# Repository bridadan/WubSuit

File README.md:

WubSuit
=======

EECS 373 final project

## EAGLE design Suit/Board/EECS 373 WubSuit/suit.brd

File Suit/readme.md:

This is where the suit code/files live...

Protocol
========
TX: | 0x00 | 0x(xdata) | 0x(ydata) | 0x(zdata) | 0x(flex) | 0x(height) | 

RX: every byte sent to LED controller 

DIO0: Note capture button 

DIO1: Left foot piezo trigger 

DIO2: Right foot piezo trigger 

DIO3: BTN 1 

DIO4: BTN 2 

DIO5: BTN 3

DIO6: BTN 4 

Arduino
=======
Contains the arduino code / files for programming on the ATMEGA328

Board
=======
Eagle files for the custom circuitboard

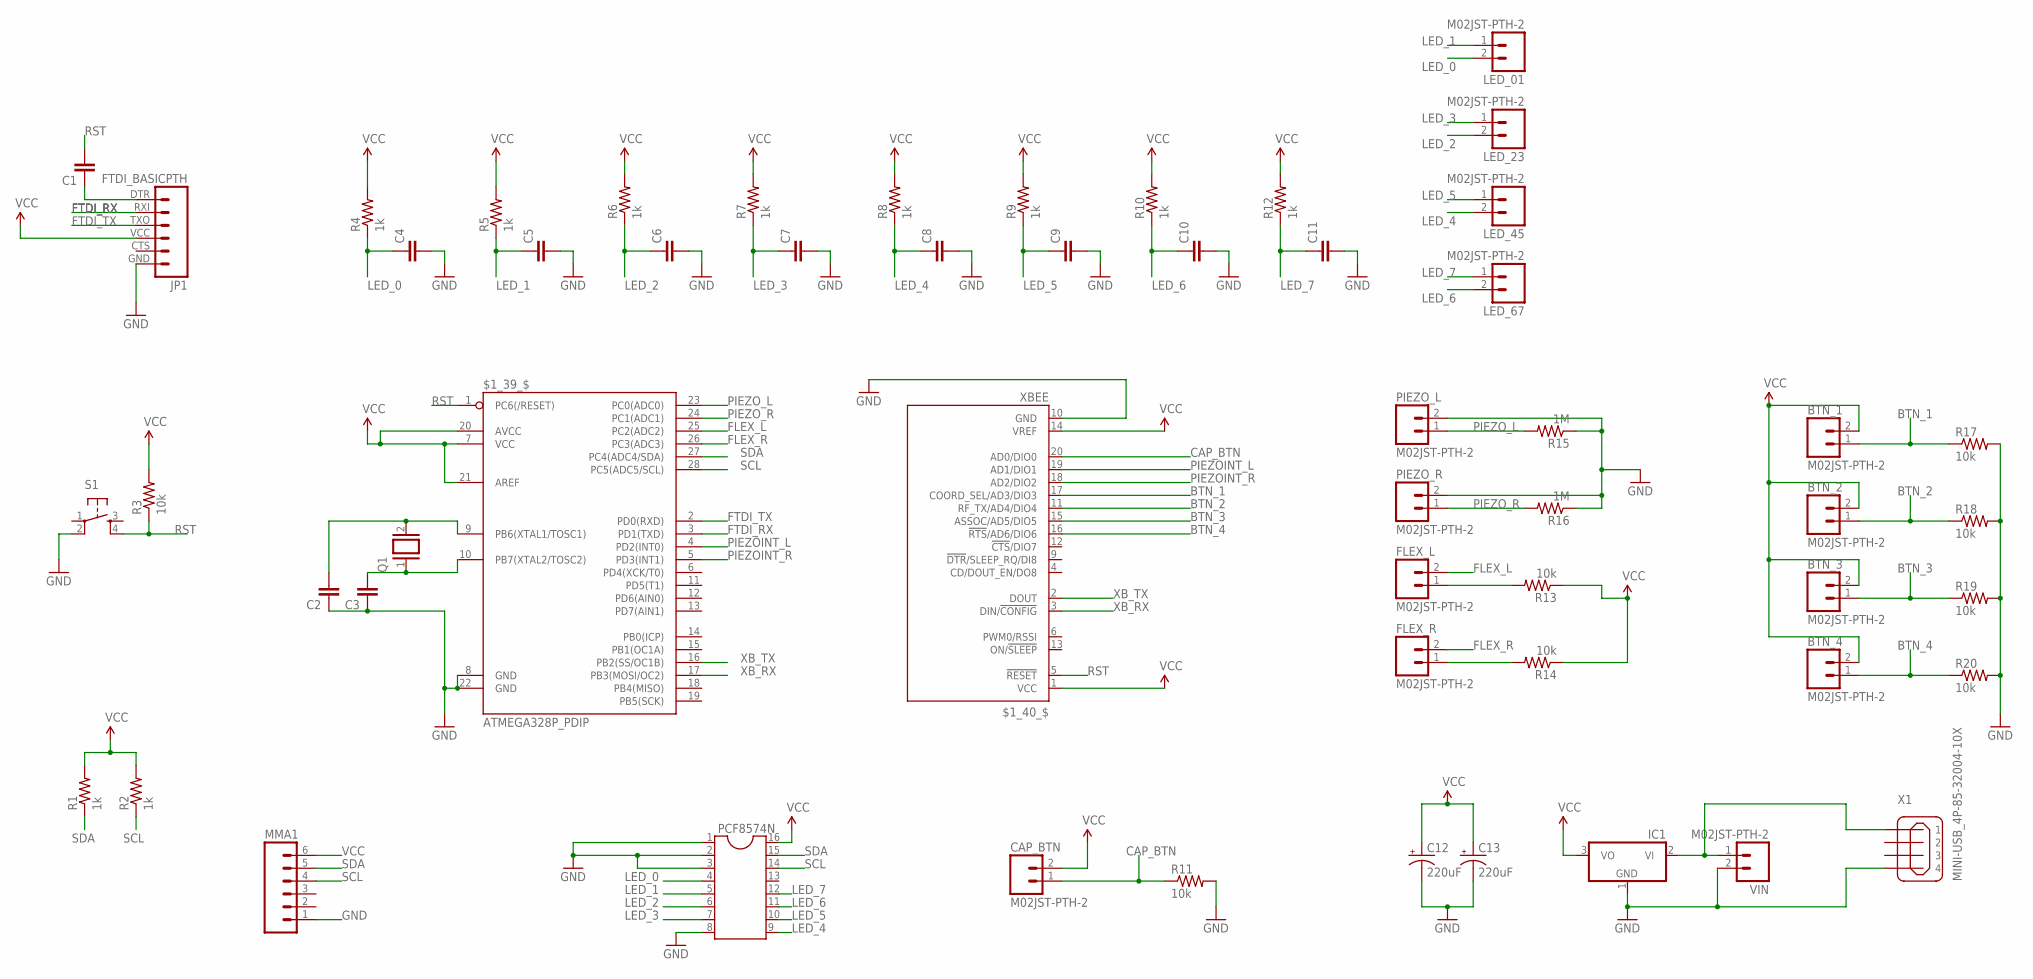
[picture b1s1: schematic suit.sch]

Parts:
$1_39_$: ATMEGA328P_PDIP; DIL28-3
$1_40_$: XBEE
BTN_1, BTN_2, BTN_3, BTN_4: M02JST-PTH-2; JST-2-PTH
C1, C2, C3, C4, C5, C6, C7, C8, C9, C10, C11: CAPEZ; CAP-PTH-SMALLEZ
C12, C13: 220uF; B45181A
CAP_BTN: M02JST-PTH-2; JST-2-PTH
FLEX_L: M02JST-PTH-2; JST-2-PTH
FLEX_R: M02JST-PTH-2; JST-2-PTH
IC1: 79L05Z; TO92
JP1: FTDI_BASICPTH; FTDI_BASIC
LED_01, LED_23, LED_45, LED_67: M02JST-PTH-2; JST-2-PTH
MMA1: M06FEMALE_LOCK; 1X06_FEMALE_LOCK.010
PCF8574N: DIL16S; SOCKET-16
PIEZO_L: M02JST-PTH-2; JST-2-PTH
PIEZO_R: M02JST-PTH-2; JST-2-PTH
Q1: XTAL/S; QS
R1, R2, R4, R5, R6, R7, R8, R9, R10, R12: 1k; 0207/10
R3, R11, R13, R14, R17, R18, R19, R20: 10k; 0207/10
R15, R16: 1M; 0207/10
S1: TAC_SWITCHPTH; TACTILE-PTH
VIN: M02JST-PTH-2; JST-2-PTH
X1: MINI-USB_4P-85-32004-10X; 85-32004-10X

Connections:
BTN_1: $1_40_$.17 (COORD_SEL/AD3/DIO3), BTN_1.1, R17.1
BTN_2: $1_40_$.11 (RF_TX/AD4/DIO4), BTN_2.1, R18.1
BTN_3: $1_40_$.15 (ASSOC/AD5/DIO5), BTN_3.1, R19.1
BTN_4: $1_40_$.16 (!RTS!/AD6/DIO6), BTN_4.1, R20.1
CAP_BTN: $1_40_$.20 (AD0/DIO0), CAP_BTN.1, R11.1
FLEX_L: $1_39_$.25 (PC2(ADC2)), FLEX_L.2
FLEX_R: $1_39_$.26 (PC3(ADC3)), FLEX_R.2
FTDI_RX: $1_39_$.3 (PD1(TXD)), JP1.RXI (2)
FTDI_TX: $1_39_$.2 (PD0(RXD)), JP1.TXO (3)
GND: $1_39_$.8 (GND), $1_39_$.22 (GND), $1_40_$.10 (GND), C2.1, C3.1, C4.2, C5.2, C6.2, C7.2, C8.2, C9.2, C10.2, C11.2, C12.-, C13.-, IC1.1 (GND), JP1.GND (6), MMA1.1, PCF8574N.1, PCF8574N.2, PCF8574N.3, PCF8574N.8, PIEZO_L.2, PIEZO_R.2, R11.2, R15.1, R16.1, R17.2, R18.2, R19.2, R20.2, S1.2, VIN.2, X1.4
LED_0: C4.1, LED_01.2, PCF8574N.4, R4.1
LED_1: C5.1, LED_01.1, PCF8574N.5, R5.1
LED_2: C6.1, LED_23.2, PCF8574N.6, R6.1
LED_3: C7.1, LED_23.1, PCF8574N.7, R7.1
LED_4: C8.1, LED_45.2, PCF8574N.9, R8.1
LED_5: C9.1, LED_45.1, PCF8574N.10, R9.1
LED_6: C10.1, LED_67.2, PCF8574N.11, R10.1
LED_7: C11.1, LED_67.1, PCF8574N.12, R12.1
unnamed: FLEX_L.1, R13.2
unnamed: FLEX_R.1, R14.2
unnamed: C1.1, JP1.DTR (1)
unnamed: $1_39_$.10 (PB7(XTAL2/TOSC2)), C3.2, Q1.1
unnamed: $1_39_$.9 (PB6(XTAL1/TOSC1)), C2.2, Q1.2
unnamed: IC1.2 (VI), VIN.1, X1.1
PIEZOINT_L: $1_39_$.4 (PD2(INT0)), $1_40_$.19 (AD1/DIO1)
PIEZOINT_R: $1_39_$.5 (PD3(INT1)), $1_40_$.18 (AD2/DIO2)
PIEZO_L: $1_39_$.23 (PC0(ADC0)), PIEZO_L.1, R15.2
PIEZO_R: $1_39_$.24 (PC1(ADC1)), PIEZO_R.1, R16.2
RST: $1_39_$.1 (PC6(/RESET)), $1_40_$.5 (!RESET), C1.2, R3.1, S1.4
SCL: $1_39_$.28 (PC5(ADC5/SCL)), MMA1.4, PCF8574N.14, R2.1
SDA: $1_39_$.27 (PC4(ADC4/SDA)), MMA1.5, PCF8574N.15, R1.1
VCC: $1_39_$.7 (VCC), $1_39_$.20 (AVCC), $1_39_$.21 (AREF), $1_40_$.1 (VCC), $1_40_$.14 (VREF), BTN_1.2, BTN_2.2, BTN_3.2, BTN_4.2, C12.+, C13.+, CAP_BTN.2, IC1.3 (VO), JP1.VCC (4), MMA1.6, PCF8574N.16, R1.2, R2.2, R3.2, R4.2, R5.2, R6.2, R7.2, R8.2, R9.2, R10.2, R12.2, R13.1, R14.1
XB_RX: $1_39_$.17 (PB3(MOSI/OC2)), $1_40_$.3 (DIN/!CONFIG)
XB_TX: $1_39_$.16 (PB2(SS/OC1B)), $1_40_$.2 (DOUT)

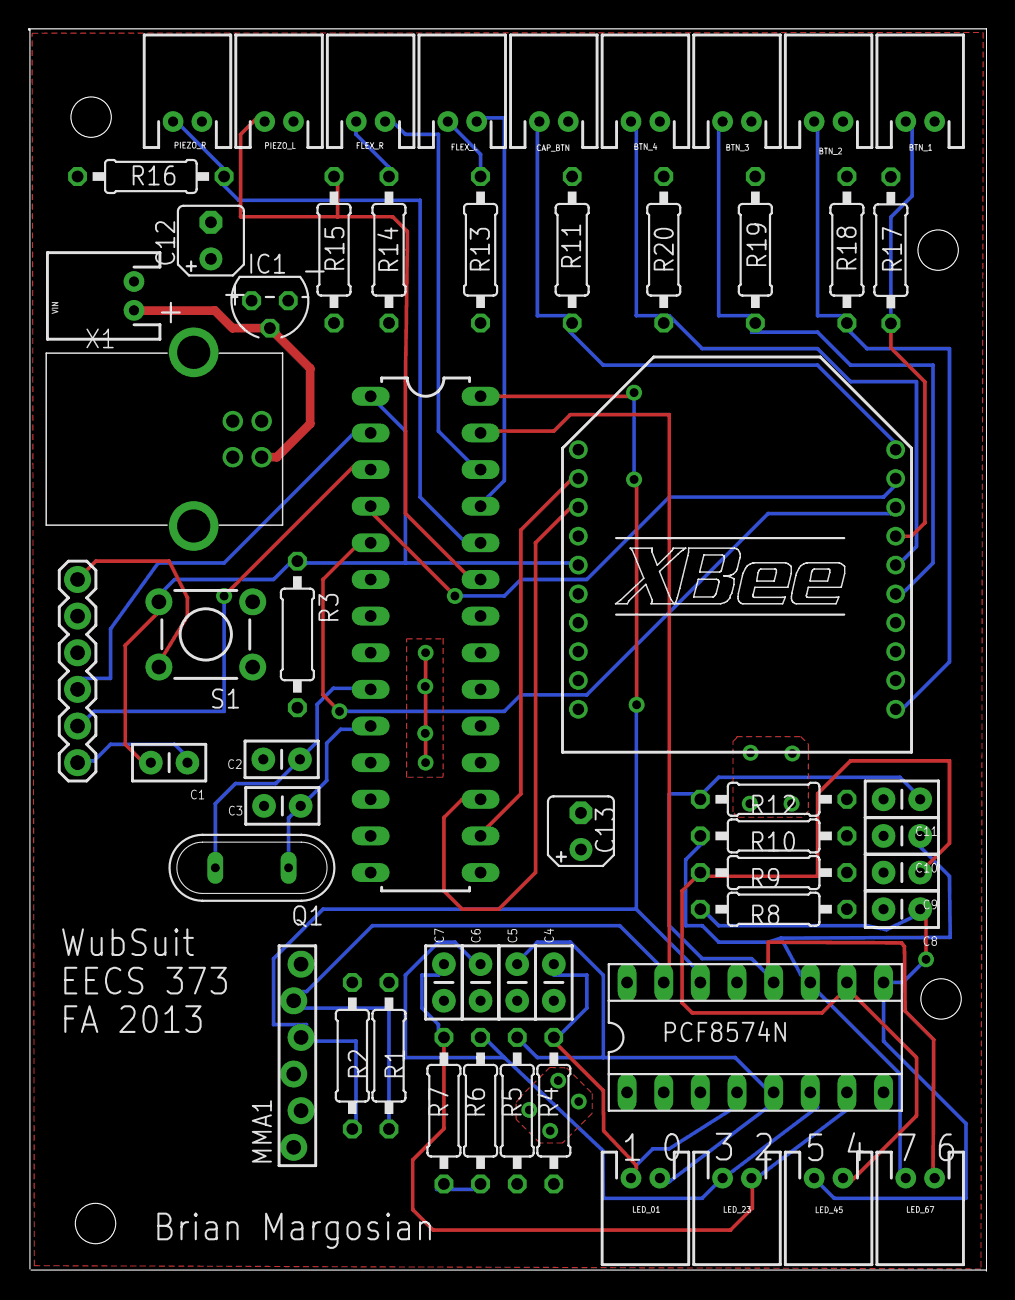
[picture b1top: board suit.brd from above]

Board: 2 copper layers, 66.4 x 86.1 mm, 56 parts (0 on the bottom side), 34 nets.

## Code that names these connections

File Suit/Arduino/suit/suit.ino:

#include <SimpleTimer.h>

#include <SoftwareSerial.h>
#include <Wire.h> //I2C

SoftwareSerial Xbee(10, 11); // RX, TX
SimpleTimer timer;
SimpleTimer resetTime;

#define DEBUG //unset if not debugging

#define PRECISION 0x02 //0x00 = 2G, 0x01 = 4G, 0x02 = 8G

#define LEDOUT_ADDR 0x20
#define ACCEL_ADDR 0x1D
#define ACCEL_X_MSB 0x01
#define ACCEL_CTRL 0x2A
#define ACCEL_XYZCFG 0x0E

#define PIEZO_L A0
#define PIEZO_R A1
#define FLEX_L A2
#define FLEX_R A3

#define SONAR 7
#define LEDPIN 13
#define TAP_L 2
#define TAP_R 3

#define FLEX_LOW 200
#define FLEX_HIGH 500
#define SONAR_LOW 0
#define SONAR_HIGH 72
#define THRESHOLD 50

byte Ax = 0x00;
byte Ay = 0x00;
byte Az = 0x00;
byte flex = 0x00;
byte height = 0x00;

boolean accel = true;

void setup()  
{
  Wire.begin(); //i2c master A5:SCL A4:SDA
  timer.setInterval(50,sendPacket);
  resetTime.setInterval(5000,softReset);
  
  // Open local serial port for debugging:
  Serial.begin(115200);

  // Open XBee serial for mass data communication
  Xbee.begin(115200);
  
  //Configure pins
  pinMode(LEDPIN,OUTPUT);
  pinMode(SONAR,INPUT);
  pinMode(TAP_L,OUTPUT);
  pinMode(TAP_R,OUTPUT);
  
  //turn the default 0xFF LEDs to all off
  setLEDs(0x00);
  
  //enable the arduino watchdog for 5 seconds.
  //wdt_enable (WDTO_4S);
  
  //init accel
  initAccel();
}

void loop()
{
  timer.run();
  resetTime.run();
  printDebug();
  updateAccel(Ax,Ay,Az);
  
  //write every recieved xbee byte to the leds
  while(Xbee.available()){
    setLEDs(Xbee.read());
  }
  int tap = 0;
  if((tap=analogRead(PIEZO_L)) > THRESHOLD){
    Serial.print("Left tap: ");
    Serial.println(tap);
    pulse(TAP_L);
    pulse(LEDPIN);
  }
  
  if((tap=analogRead(PIEZO_R)) > THRESHOLD){
    Serial.print("Right tap: ");
    Serial.println(tap);
    pulse(TAP_R);
    pulse(LEDPIN);
  }
  byte lastheight = height;
  height = map(pulseIn(SONAR,HIGH,10000)/147,SONAR_LOW,SONAR_HIGH,0,254);
  if(height == 0)
    height = lastheight; //pulseIn broke, so keep valid data.
  flex = map(analogRead(FLEX_L),FLEX_LOW,FLEX_HIGH,0,254);
}

void setLEDs(byte data){
  //Writes a byte to the LED strip via i2c
    Wire.beginTransmission(LEDOUT_ADDR);
    Wire.write(data); //active high
    Wire.endTransmission();
    
    #ifdef DEBUG
      Serial.print("Wrote LEDs to: ");
      Serial.println((byte)(data),BIN);
    #endif
}

void sendPacket(){
  //send a packet of data to UART 
  if(Xbee.overflow()){
   Serial.println("Xbee overflow");
   return; 
  }
  noInterrupts();
  Xbee.write((byte)0xFF);
  Xbee.write((byte)0xA0);
  Xbee.write((byte)0xB7);
  Xbee.write(Ax);
  Xbee.write(Ay);
  Xbee.write(Az);
  Xbee.write(flex);
  Xbee.write(height);
  interrupts();
}

void pulse(int pin){
 //pulses a pin for one cycle
 //assumes pin is declared as output
 digitalWrite(pin, HIGH);  
 delay(10);
 digitalWrite(pin, LOW); 
}

void initAccel(){
  //make sure the accelerometer is actually there
  byte whoamI = 0x00;
  Wire.beginTransmission(ACCEL_ADDR);
  Wire.write(0x0D);
  Wire.endTransmission(false); //waits for data
  Wire.requestFrom(ACCEL_ADDR,1);
  for(int i=0;(i<1000) && !Wire.available();i++); //hang out
  whoamI = Wire.read();
  
  if(whoamI != 0x2A){
    accel = false;
    Serial.println("Accelerometer not available.");
    return;
  }
  
  //first we get the status of the ctrl reg
  Wire.beginTransmission(ACCEL_ADDR);
  Wire.write(ACCEL_CTRL);
  Wire.endTransmission(false); //waits for data
  Wire.requestFrom(ACCEL_ADDR,1);
  while(!Wire.available()); //hang out until available
  byte ctrl = Wire.read();
  
  //now we throw it in standby to edit ctrl reg
  Wire.beginTransmission(ACCEL_ADDR);
  Wire.write(ACCEL_CTRL);
  Wire.write(ctrl & ~(0x01)); //clears active bit
  Wire.endTransmission();
  
  //write the scale
  Wire.beginTransmission(ACCEL_ADDR);
  Wire.write(ACCEL_XYZCFG);
  Wire.write(PRECISION); //set precision
  Wire.endTransmission();
  
  //throw it back into active
  Wire.beginTransmission(ACCEL_ADDR);
  Wire.write(ACCEL_CTRL);
  Wire.write(ctrl | 0x01); //sets active bit, if not set
  Wire.endTransmission();
}

void updateAccel(byte &x,byte &y,byte &z){
  if(!accel) return; //accel not available
  //pulls data from the accelerometer on the I2C bus
  //and places it into the x, y, and z parameters
  byte data[6];
  Wire.beginTransmission(ACCEL_ADDR);
  Wire.write(ACCEL_X_MSB);
  Wire.endTransmission(false); //this ends the write, but waits for the response
  
  Wire.requestFrom(ACCEL_ADDR,6); //6 bytes: Xhigh,low Yhigh,low Zhigh,low
  while(Wire.available() < 6){}; //wait until they all appear in the buffer
  
  for(int i=0; i<6; i++){
    data[i] = Wire.read(); //empty the buffer into the data array
    if(data[i] == 0xFF) //don't invalizate packet structure
      data[i] = 0xFE;
  }
  
   //x = map((data[0]<<8 | data[1])/2,0,0xFFFF,0,0xFE);
   //y = map((data[2]<<8 | data[3])/2,0,0xFFFF,0,0xFE);
   //z = map((data[4]<<8 | data[5])/2,0,0xFFFF,0,0xFE);
   x = data[0];
   y = data[2];
   z = data[4];
}

void printDebug(){
  if(Serial.available()){
   //process debug data first
   char input = Serial.read(); //r: flexR, l: flexL, x:accelX, y,z same, w(char) write LED,
   switch(input){
    case 'r':
      Serial.println(analogRead(FLEX_R));
      break;
    case 'l':
      Serial.println(analogRead(FLEX_L));
      break;
    case 'x':
      Serial.println(Ax);
      break;
    case 'y':
      Serial.println(Ay);
      break;
    case 'z':
      Serial.println(Az);
      break;
    case 'w':
      setLEDs((int)Serial.read());
      break;
    default:
      Serial.println("Not supported");
      break;
   } 
  }
}

void softReset() // Restarts program from beginning but does not reset the peripherals and registers
{
  asm volatile ("  jmp 0");  
}

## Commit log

2013-11-05 Initial commit -Basic MIDI driver implemented, needs to be tested on actual hardware
2013-11-07 added ultrasonic timer stuff
2013-11-08 Reorganized file structure
2013-11-08 Fixed some readmes
2013-11-08 added dummy files so folders will show up
2013-11-13 started arduino code
2013-11-15 Started work on PCB
2013-11-19 Redid Libero project -Added 3 UART modules for MIDI, XBee, and LCD -Added 4 interrupts, 2 for RX on UART, 2 for CapButton and LPiezo
2013-11-20 Finished (somewhat) the arduino code, proto bard is ready, working on eagle design
2013-11-20 fixed some stuff
2013-11-20 added more board/sch files
2013-11-20 working on board layout and routing
2013-11-21 almost done with the board layout and routing, need to add power headers
2013-11-21 Added some more UART Logic and added ground work for suit state and menus
2013-11-21 finished and ordered board
2013-11-25 Menu work and UART refinements
2013-11-25 Fixed menu function pointer errors, XBee tested and working
2013-11-26 Checkpoint commit before refactoring menus
2013-11-26 Need to test and add some more functionality for menus, close to being finished -Need to write redrawing logic for menu options that have values
2013-11-26 Menu testing -Need to add some state so that MIDI interrupt know to map to a value
2013-12-02 worked on Arduino code
2013-12-03 checkpoint commit before merge
2013-12-03 another checkpoint commit
2013-12-03 Menus almost completely working, printing status screen to LCD with dummy commands -Problem when reading in large MIDI message (specifically when play button pressed in FL studio), overwritting memor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
2013-12-03 more arduino work
2013-12-03 LCD Functions added and MIDI RX buffer overflow fixed -Ditched the erase block function for LCD, couldn't get it working. Instead, I'm printing spaces to the spots that need to be cleared
2013-12-04 More arduino work, added values to some resistors in eagle
2013-12-05 began working on poster design
2013-12-08 Software and Libero update -added timer interrupt for LCD -Still need change XBee UART
2013-12-08 Working on poster, almost done, just need a little more text
2013-12-08 Updated Arduino code to use only left flex sensor and send 3 bytes for each start of packet - 3 bytes are 0xFF 0xA0 0xB7
2013-12-10 finished arduino code, fixed PCB error
2013-12-10 Final commit! Whooohooo (until we find more bugs lololololol)
2013-12-10 final arduino work mid-demo

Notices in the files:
parts and their libraries:
SparkFun-DigitalIC: Licensing: CC v3.0 Share-Alike You are welcome to use this library for commercial purposes.
